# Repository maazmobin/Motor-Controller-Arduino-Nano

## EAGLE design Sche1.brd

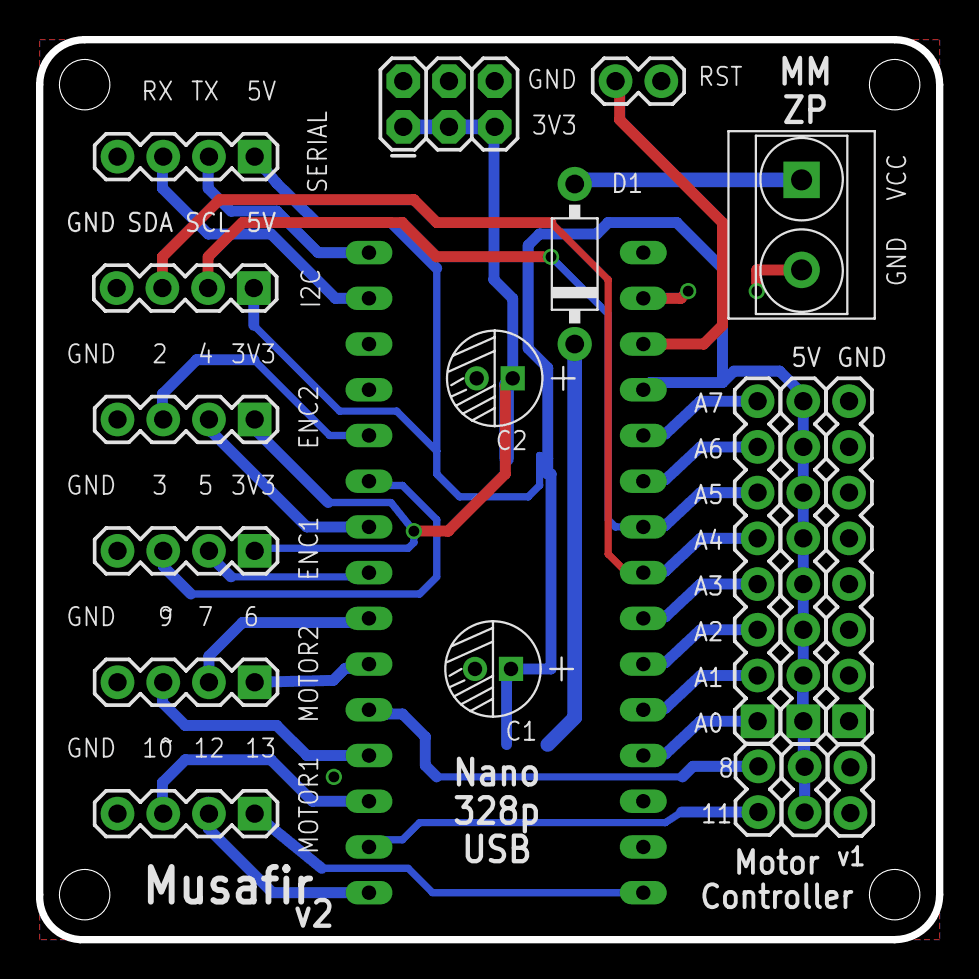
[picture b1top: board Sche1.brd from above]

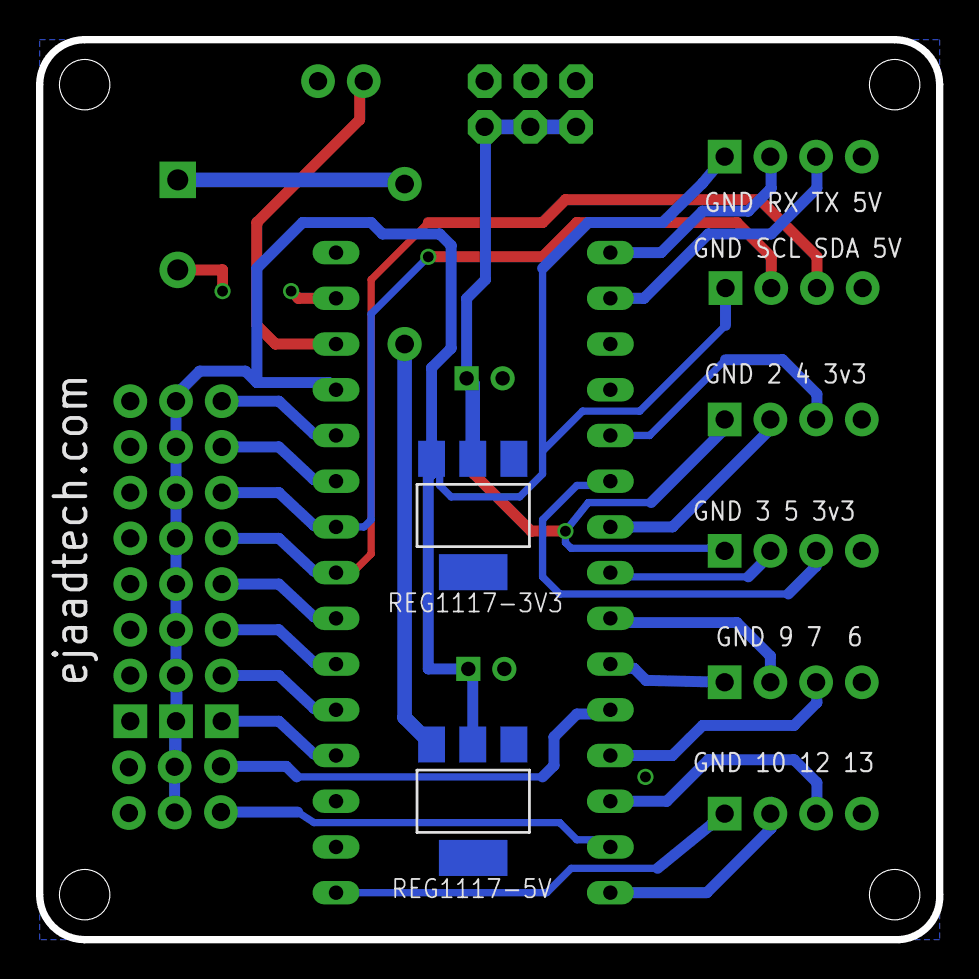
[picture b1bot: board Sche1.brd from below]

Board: 2 copper layers, 50.0 x 50.0 mm, 21 parts (2 on the bottom side), 28 nets.

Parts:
3V3_GND: FEMALE 2x3; 2X3
5V1: 1X02
5V2: 1X08
ANALOG: 1X08
C1, C2: 100uf; PC-D5.3MM
D1: 1N4004; DO-41
D8D11: 1X02
ENC1, ENC2: 1X04
GND1: 1X02
GND2: 1X08
I2C: 1X04
MOTOR1, MOTOR2: 1X04
POWER: GREEN-2P-5.0; H2-5.0-10.5X8.0MM
REG1117-3V3, REG1117-5V: REG1117; SOT223
RST: 1X02
SERIAL: 1X04
U$1: NANO

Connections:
3V3: 3V3_GND.1, 3V3_GND.3, 3V3_GND.5, C2.+, ENC1.1, ENC2.1, REG1117-3V3.2
5V: 5V1.1, 5V1.2, 5V2.1, 5V2.2, 5V2.3, 5V2.4, 5V2.5, 5V2.6, 5V2.7, 5V2.8, C1.+, I2C.1, REG1117-3V3.3, REG1117-5V.2, SERIAL.1, U$1.5V
A0: ANALOG.1, U$1.A0
A1: ANALOG.2, U$1.A1
A2: ANALOG.3, U$1.A2
A3: ANALOG.4, U$1.A3
A4: ANALOG.5, I2C.3, U$1.A4
A5: ANALOG.6, I2C.2, U$1.A5
A6: ANALOG.7, U$1.A6
A7: ANALOG.8, U$1.A7
D2: ENC2.3, U$1.D2
D3: ENC1.3, U$1.D3
D4: ENC2.2, U$1.D4
D5: ENC1.2, U$1.D5
D6: MOTOR2.2, U$1.D6
D7: MOTOR2.1, U$1.D7
D8: D8D11.1, U$1.D8
D9: MOTOR2.3, U$1.D9
D10: MOTOR1.3, U$1.D10
D11: D8D11.2, U$1.D11
D12: MOTOR1.2, U$1.D12
D13: MOTOR1.1, U$1.D13
GND: 3V3_GND.2, 3V3_GND.4, 3V3_GND.6, C1.-, C2.-, ENC1.4, ENC2.4, GND1.1, GND1.2, GND2.1, GND2.2, GND2.3, GND2.4, GND2.5, GND2.6, GND2.7, GND2.8, I2C.4, MOTOR1.4, MOTOR2.4, POWER.2, REG1117-3V3.1, REG1117-5V.1, RST.2, SERIAL.4, U$1.GND, U$1.GND1
unnamed: D1.1, POWER.1
RST: RST.1, U$1.RST
RX: SERIAL.3, U$1.RX1
TX: SERIAL.2, U$1.TX0
VCC: D1.2, REG1117-5V.3

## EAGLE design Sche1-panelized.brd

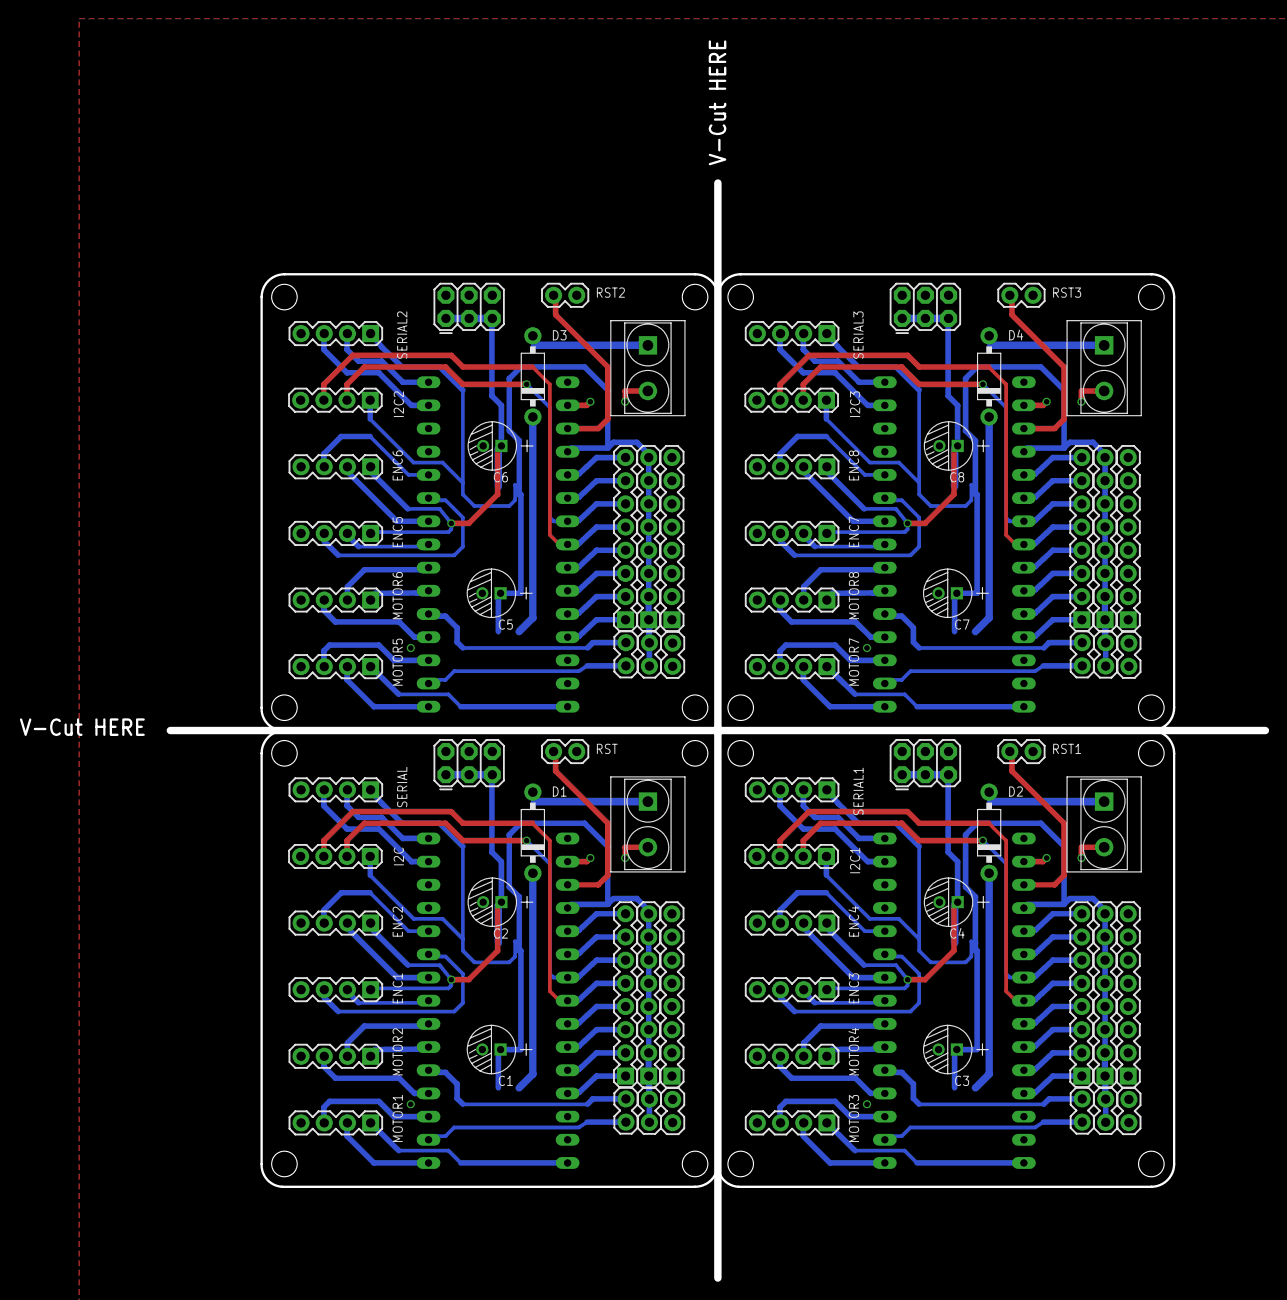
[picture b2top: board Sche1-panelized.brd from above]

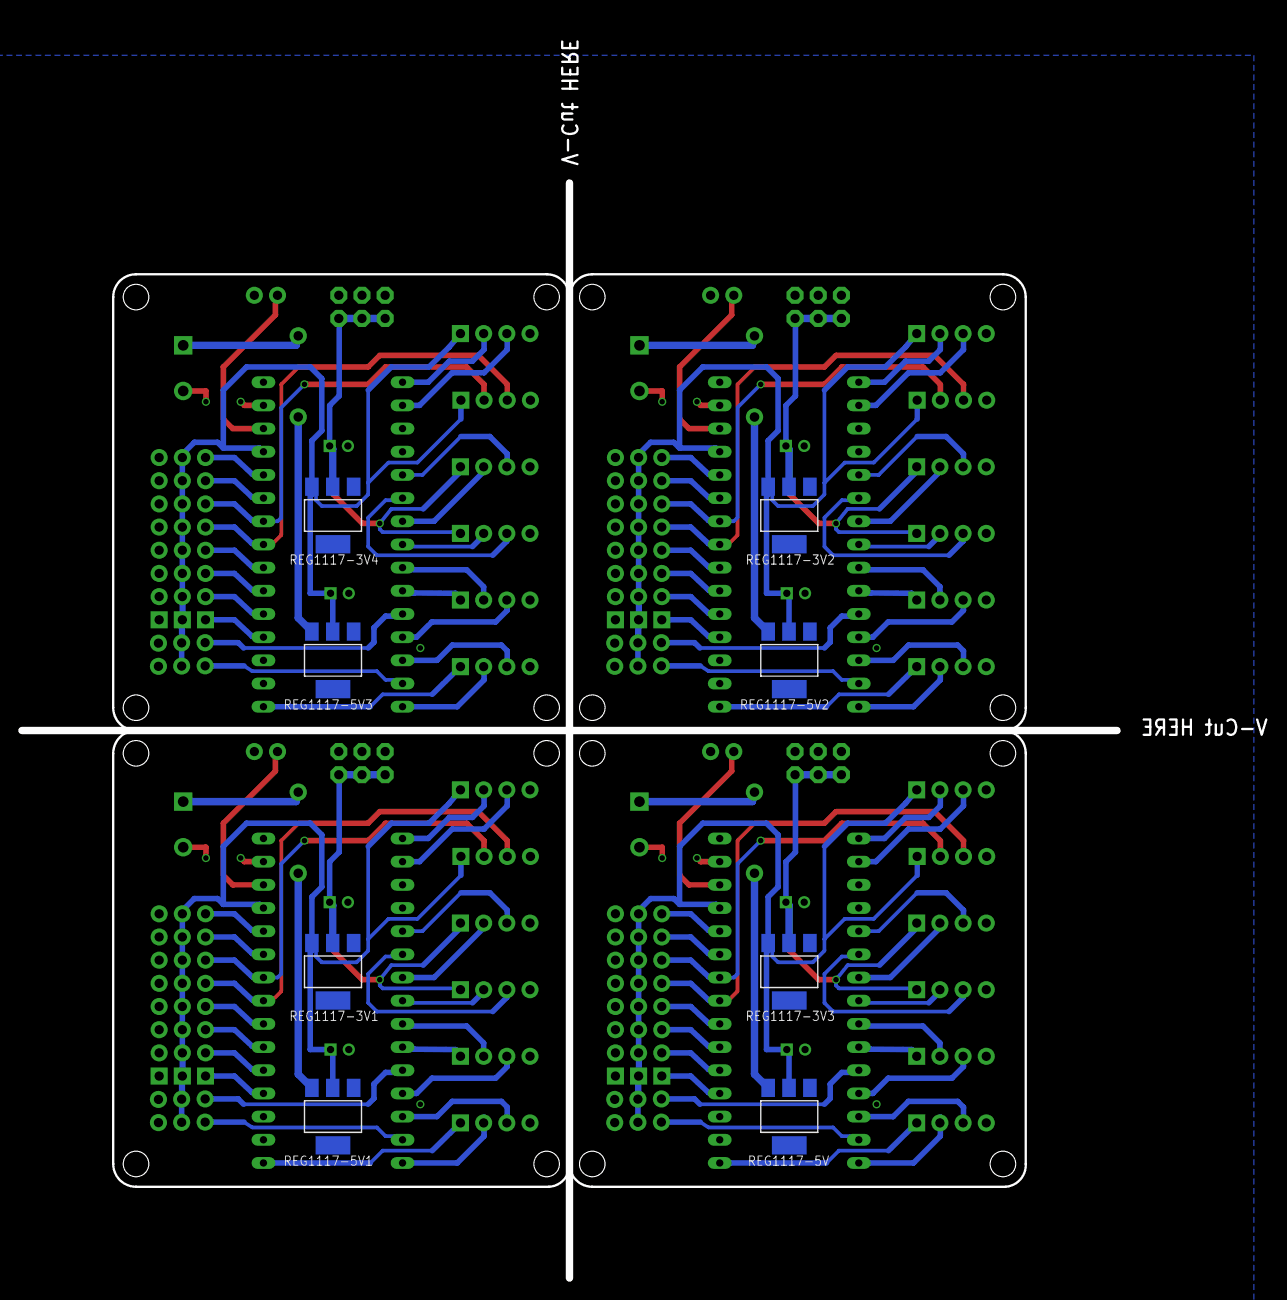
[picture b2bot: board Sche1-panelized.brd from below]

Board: 2 copper layers, 100.0 x 100.0 mm, 84 parts (8 on the bottom side), 109 nets.

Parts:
3V3_GND, 3V3_GND1, 3V3_GND2, 3V3_GND3: FEMALE 2x3; 2X3
5V1, 5V3, 5V5, 5V7: 1X02
5V2, 5V4, 5V6, 5V8: 1X08
ANALOG, ANALOG1, ANALOG2, ANALOG3: 1X08
C1, C2, C3, C4, C5, C6, C7, C8: 100uf; PC-D5.3MM
D1, D2, D3, D4: 1N4004; DO-41
D8D1, D8D2, D8D3, D8D11: 1X02
ENC1, ENC2, ENC3, ENC4, ENC5, ENC6, ENC7, ENC8: 1X04
GND1, GND3, GND5, GND7: 1X02
GND2, GND4, GND6, GND8: 1X08
I2C, I2C1, I2C2, I2C3: 1X04
MOTOR1, MOTOR2, MOTOR3, MOTOR4, MOTOR5, MOTOR6, MOTOR7, MOTOR8: 1X04
POWER, POWER1, POWER2, POWER3: GREEN-2P-5.0; H2-5.0-10.5X8.0MM
REG1117-3V1, REG1117-3V2, REG1117-3V3, REG1117-3V4, REG1117-5V, REG1117-5V1, REG1117-5V2, REG1117-5V3: REG1117; SOT223
RST, RST1, RST2, RST3: 1X02
SERIAL, SERIAL1, SERIAL2, SERIAL3: 1X04
U$1, U$2, U$3, U$4: NANO

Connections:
3V1: 3V3_GND1.1, 3V3_GND1.3, 3V3_GND1.5, C4.+, ENC3.1, ENC4.1, REG1117-3V1.2
3V2: 3V3_GND2.1, 3V3_GND2.3, 3V3_GND2.5, C6.+, ENC5.1, ENC6.1, REG1117-3V2.2
3V3: 3V3_GND.1, 3V3_GND.3, 3V3_GND.5, C2.+, ENC1.1, ENC2.1, REG1117-3V3.2
3V4: 3V3_GND3.1, 3V3_GND3.3, 3V3_GND3.5, C8.+, ENC7.1, ENC8.1, REG1117-3V4.2
5V: 5V1.1, 5V1.2, 5V2.1, 5V2.2, 5V2.3, 5V2.4, 5V2.5, 5V2.6, 5V2.7, 5V2.8, C1.+, I2C.1, REG1117-3V3.3, REG1117-5V.2, SERIAL.1, U$1.5V
5V1: 5V3.1, 5V3.2, 5V4.1, 5V4.2, 5V4.3, 5V4.4, 5V4.5, 5V4.6, 5V4.7, 5V4.8, C3.+, I2C1.1, REG1117-3V1.3, REG1117-5V1.2, SERIAL1.1, U$2.5V
5V2: 5V5.1, 5V5.2, 5V6.1, 5V6.2, 5V6.3, 5V6.4, 5V6.5, 5V6.6, 5V6.7, 5V6.8, C5.+, I2C2.1, REG1117-3V2.3, REG1117-5V2.2, SERIAL2.1, U$3.5V
5V3: 5V7.1, 5V7.2, 5V8.1, 5V8.2, 5V8.3, 5V8.4, 5V8.5, 5V8.6, 5V8.7, 5V8.8, C7.+, I2C3.1, REG1117-3V4.3, REG1117-5V3.2, SERIAL3.1, U$4.5V
A0: ANALOG.1, U$1.A0
A1: ANALOG.2, U$1.A1
A2: ANALOG.3, U$1.A2
A3: ANALOG.4, U$1.A3
A4: ANALOG.5, I2C.3, U$1.A4
A5: ANALOG.6, I2C.2, U$1.A5
A6: ANALOG.7, U$1.A6
A7: ANALOG.8, U$1.A7
A8: ANALOG1.6, I2C1.2, U$2.A5
A9: ANALOG1.5, I2C1.3, U$2.A4
A10: ANALOG1.1, U$2.A0
A11: ANALOG1.2, U$2.A1
A12: ANALOG1.3, U$2.A2
A13: ANALOG1.4, U$2.A3
A14: ANALOG1.7, U$2.A6
A15: ANALOG1.8, U$2.A7
A16: ANALOG2.6, I2C2.2, U$3.A5
A17: ANALOG2.5, I2C2.3, U$3.A4
A18: ANALOG2.1, U$3.A0
A19: ANALOG2.2, U$3.A1
A20: ANALOG2.3, U$3.A2
A21: ANALOG2.4, U$3.A3
A22: ANALOG2.7, U$3.A6
A23: ANALOG2.8, U$3.A7
A24: ANALOG3.6, I2C3.2, U$4.A5
A25: ANALOG3.5, I2C3.3, U$4.A4
A26: ANALOG3.1, U$4.A0
A27: ANALOG3.2, U$4.A1
A28: ANALOG3.3, U$4.A2
A29: ANALOG3.4, U$4.A3
A30: ANALOG3.7, U$4.A6
A31: ANALOG3.8, U$4.A7
D1: MOTOR3.3, U$2.D10
D2: ENC2.3, U$1.D2
D3: ENC1.3, U$1.D3
D4: ENC2.2, U$1.D4
D5: ENC1.2, U$1.D5
D6: MOTOR2.2, U$1.D6
D7: MOTOR2.1, U$1.D7
D8: D8D11.1, U$1.D8
D9: MOTOR2.3, U$1.D9
D10: MOTOR1.3, U$1.D10
D11: D8D11.2, U$1.D11
D12: MOTOR1.2, U$1.D12
D13: MOTOR1.1, U$1.D13
D14: MOTOR3.2, U$2.D12
D15: MOTOR3.1, U$2.D13
D16: MOTOR4.1, U$2.D7
D17: MOTOR4.2, U$2.D6
D18: MOTOR4.3, U$2.D9
D19: ENC3.2, U$2.D5
D20: ENC3.3, U$2.D3
D21: ENC4.2, U$2.D4
D22: ENC4.3, U$2.D2
D23: D8D1.1, U$2.D8
D24: D8D1.2, U$2.D11
D25: MOTOR5.3, U$3.D10
D26: MOTOR5.2, U$3.D12
D27: MOTOR5.1, U$3.D13
D28: MOTOR6.1, U$3.D7
D29: MOTOR6.2, U$3.D6
D30: MOTOR6.3, U$3.D9
D31: ENC5.2, U$3.D5
D32: ENC5.3, U$3.D3
D33: ENC6.2, U$3.D4
D34: ENC6.3, U$3.D2
D35: D8D2.1, U$3.D8
D36: D8D2.2, U$3.D11
D37: MOTOR7.3, U$4.D10
D38: MOTOR7.2, U$4.D12
D39: MOTOR7.1, U$4.D13
D40: MOTOR8.1, U$4.D7
D41: MOTOR8.2, U$4.D6
D42: MOTOR8.3, U$4.D9
D43: ENC7.2, U$4.D5
D44: ENC7.3, U$4.D3
D45: ENC8.2, U$4.D4
D46: ENC8.3, U$4.D2
D47: D8D3.1, U$4.D8
D48: D8D3.2, U$4.D11
GND: 3V3_GND.2, 3V3_GND.4, 3V3_GND.6, 3V3_GND1.2, 3V3_GND1.4, 3V3_GND1.6, 3V3_GND2.2, 3V3_GND2.4, 3V3_GND2.6, 3V3_GND3.2, 3V3_GND3.4, 3V3_GND3.6, C1.-, C2.-, C3.-, C4.-, C5.-, C6.-, C7.-, C8.-, ENC1.4, ENC2.4, ENC3.4, ENC4.4, ENC5.4, ENC6.4, ENC7.4, ENC8.4, GND1.1, GND1.2, GND2.1, GND2.2, GND2.3, GND2.4, GND2.5, GND2.6, GND2.7, GND2.8, GND3.1, GND3.2, GND4.1, GND4.2, GND4.3, GND4.4, GND4.5, GND4.6, GND4.7, GND4.8, GND5.1, GND5.2, GND6.1, GND6.2, GND6.3, GND6.4, GND6.5, GND6.6, GND6.7, GND6.8, GND7.1, GND7.2, GND8.1, GND8.2, GND8.3, GND8.4, GND8.5, GND8.6, GND8.7, GND8.8, I2C.4, I2C1.4, I2C2.4, I2C3.4, MOTOR1.4, MOTOR2.4, MOTOR3.4, MOTOR4.4, MOTOR5.4, MOTOR6.4, MOTOR7.4, MOTOR8.4, POWER.2, POWER1.2, POWER2.2, POWER3.2, REG1117-3V1.1, REG1117-3V2.1, REG1117-3V3.1, REG1117-3V4.1, REG1117-5V.1, REG1117-5V1.1, REG1117-5V2.1, REG1117-5V3.1, RST.2, RST1.2, RST2.2, RST3.2, SERIAL.4, SERIAL1.4, SERIAL2.4, SERIAL3.4, U$1.GND, U$1.GND1, U$2.GND, U$2.GND1, U$3.GND, U$3.GND1, U$4.GND, U$4.GND1
unnamed: D1.1, POWER.1
unnamed: D2.1, POWER1.1
unnamed: D3.1, POWER2.1
unnamed: D4.1, POWER3.1
RST: RST.1, U$1.RST
RST1: RST1.1, U$2.RST
RST2: RST2.1, U$3.RST
RST3: RST3.1, U$4.RST
RX: SERIAL.3, U$1.RX1
RX1: SERIAL1.3, U$2.RX1
RX2: SERIAL2.3, U$3.RX1
RX3: SERIAL3.3, U$4.RX1
TX: SERIAL.2, U$1.TX0
TX1: SERIAL1.2, U$2.TX0
TX2: SERIAL2.2, U$3.TX0
TX3: SERIAL3.2, U$4.TX0
VCC: D1.2, REG1117-5V.3
VCC1: D2.2, REG1117-5V1.3
VCC2: D3.2, REG1117-5V2.3
VCC3: D4.2, REG1117-5V3.3

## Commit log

2016-12-05 :circus_tent: Added .gitattributes & .gitignore files
2016-12-05 Schematic Done
2016-12-06 pcb Completed
2016-12-08 Changes in component layout
    board layout 10% incomplete
2016-12-11 COMPLETED
    Cosmetics Required
2016-12-13 some PCB Cleanup - tracks and silk screen
2016-12-14 finalized before panelization
2016-12-14 gerbers created and in SEEED CART
2016-12-15 sent to SEEED Fusion - v2

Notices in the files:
parts and their libraries:
SparkFun-Connectors: Licensing: Creative Commons ShareAlike 4.0 International - https://creativecommons.org/licenses/by-sa/4.0
